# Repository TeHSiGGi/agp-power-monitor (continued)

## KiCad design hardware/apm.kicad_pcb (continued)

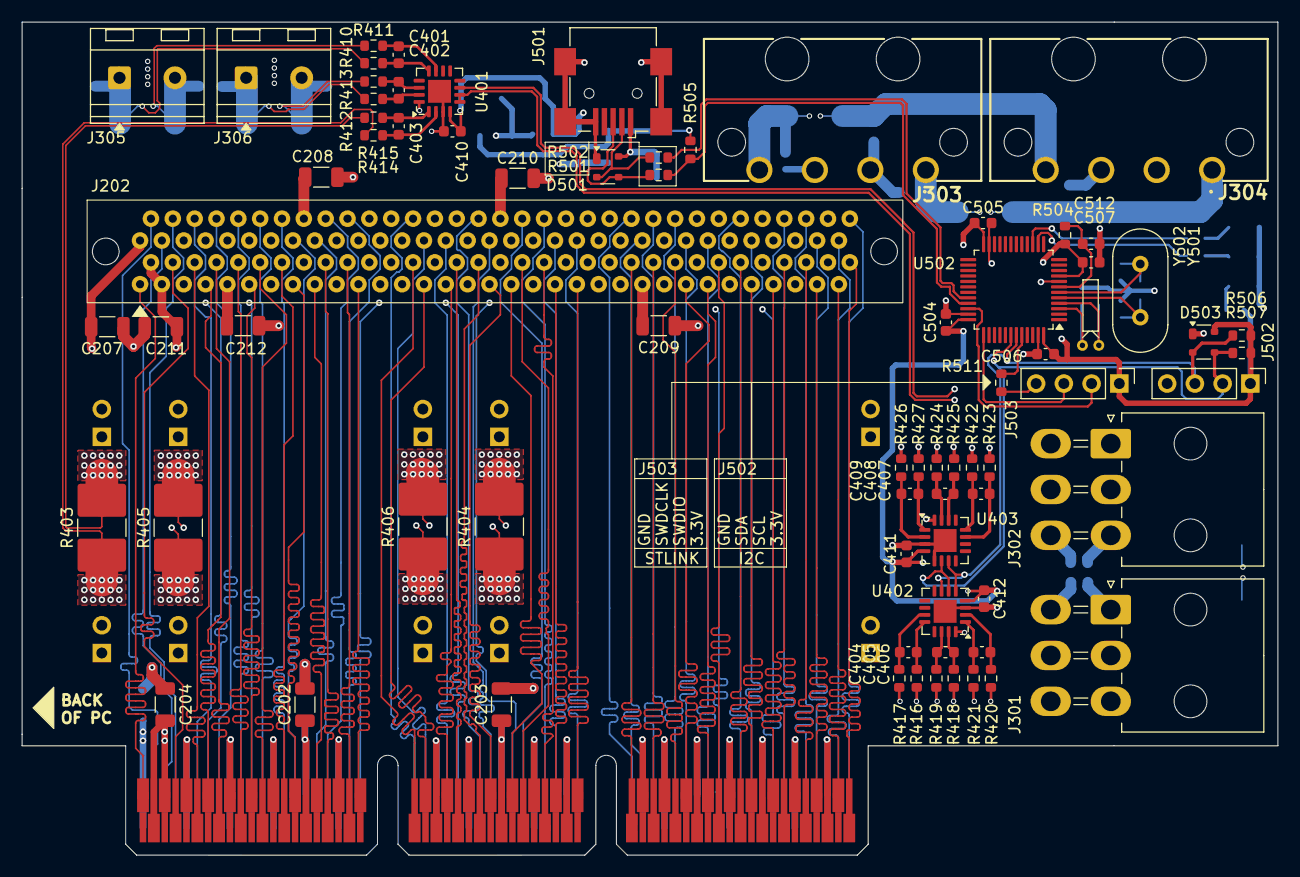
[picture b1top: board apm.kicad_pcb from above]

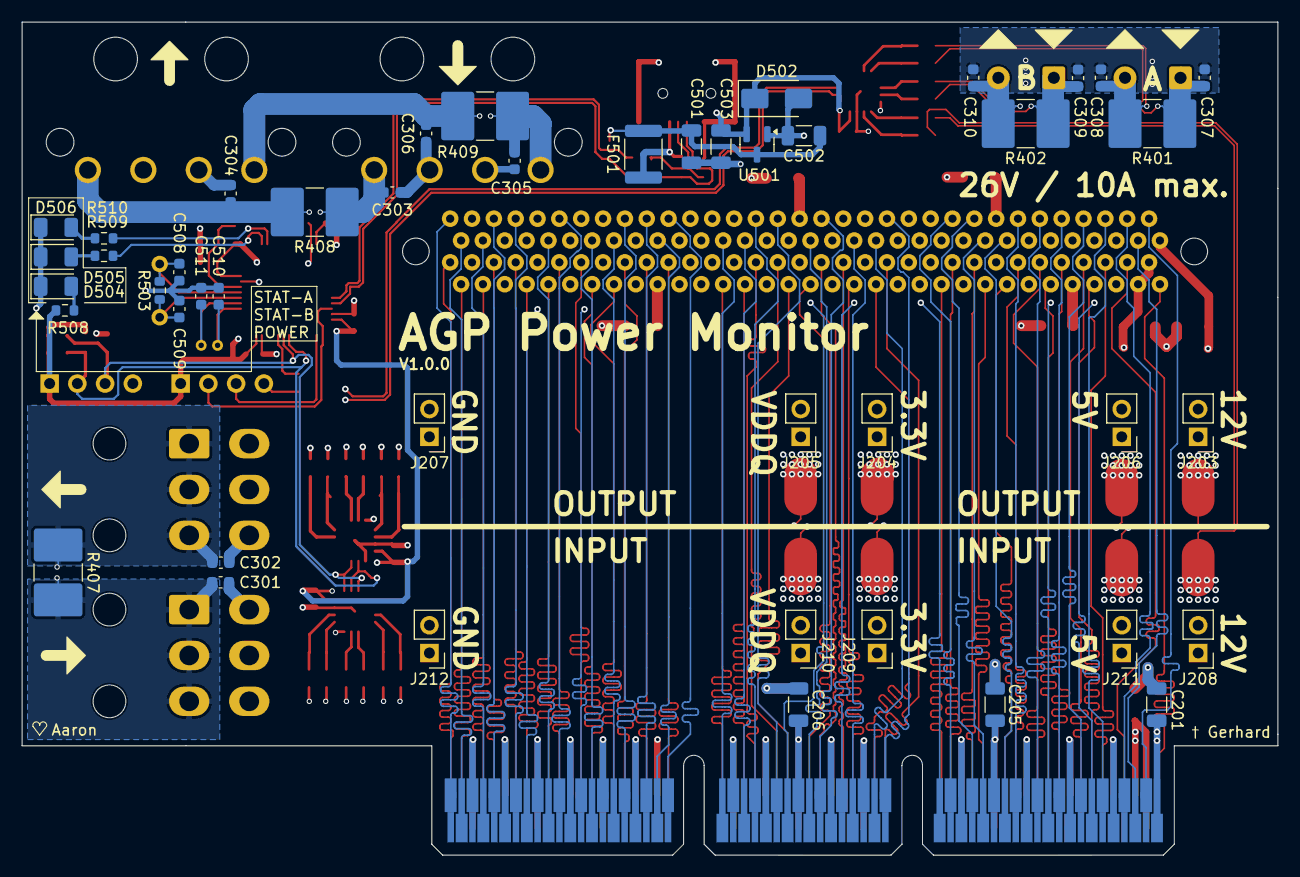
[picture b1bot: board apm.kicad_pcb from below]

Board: 4 copper layers, 115.0 x 76.3 mm, 119 parts (45 on the bottom side), 139 nets.

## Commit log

2025-06-02 missed gitignore, cleaning up
2025-06-02 added pictures
2025-06-02 added interface picture
2025-06-02 small images
2025-06-02 added small interface
2025-06-03 updating reference values to include 6800XT and 7600GS
2025-06-27 new refs
2025-06-27 begone
2025-06-27 adjusted viewer look
2025-06-27 replaced ref vals
2025-06-27 image refs
2025-07-01 more references
2025-07-02 added 6800xt and fx5200
2025-07-04 added geforce 4ti
2025-07-08 updated refs
2025-07-09 added new cards
2025-07-10 added x800xt
2025-07-12 added JSON export, windows batch
2025-07-17 using a static copy of the buffer
2025-07-18 added Geforce 2 GTS 32MB
2025-07-18 added medion geforce 3 ti 200
2025-07-23 added new cards + parallel load
2025-07-23 credits to vogons member
2025-07-23 doc format
2025-08-14 added radeon 9700 non pro
2025-10-11 added consumption charts, fixed few typos
2026-03-16 added three more cards
2026-03-16 fixed name
